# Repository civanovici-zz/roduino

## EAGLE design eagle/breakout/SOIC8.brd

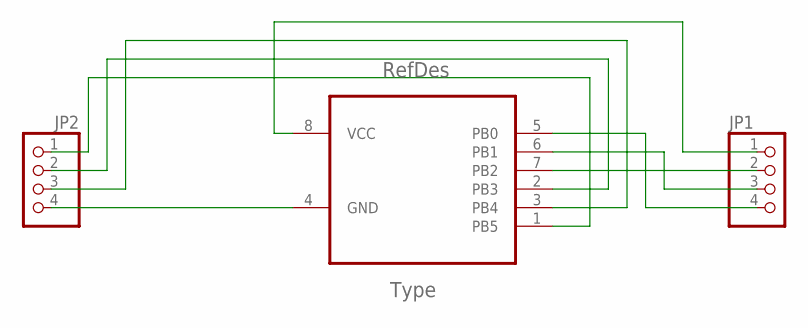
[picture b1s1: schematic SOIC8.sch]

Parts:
JP1, JP2: PINHD-1X4; 1X04
U1: ATTINY13-20SU; SOIC127P798X216-8N

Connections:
unnamed: JP2.1, U1.1 (PB5)
unnamed: JP2.2, U1.2 (PB3)
unnamed: JP2.3, U1.3 (PB4)
unnamed: JP2.4, U1.4 (GND)
unnamed: JP1.4, U1.5 (PB0)
unnamed: JP1.3, U1.6 (PB1)
unnamed: JP1.2, U1.7 (PB2)
unnamed: JP1.1, U1.8 (VCC)

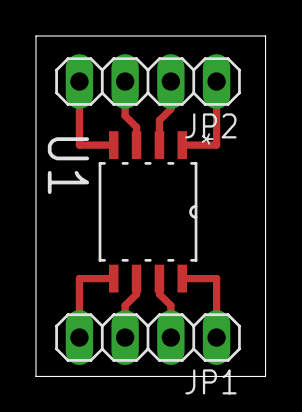
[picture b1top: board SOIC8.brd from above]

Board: 2 copper layers, 12.8 x 18.9 mm, 3 parts (0 on the bottom side), 8 nets.

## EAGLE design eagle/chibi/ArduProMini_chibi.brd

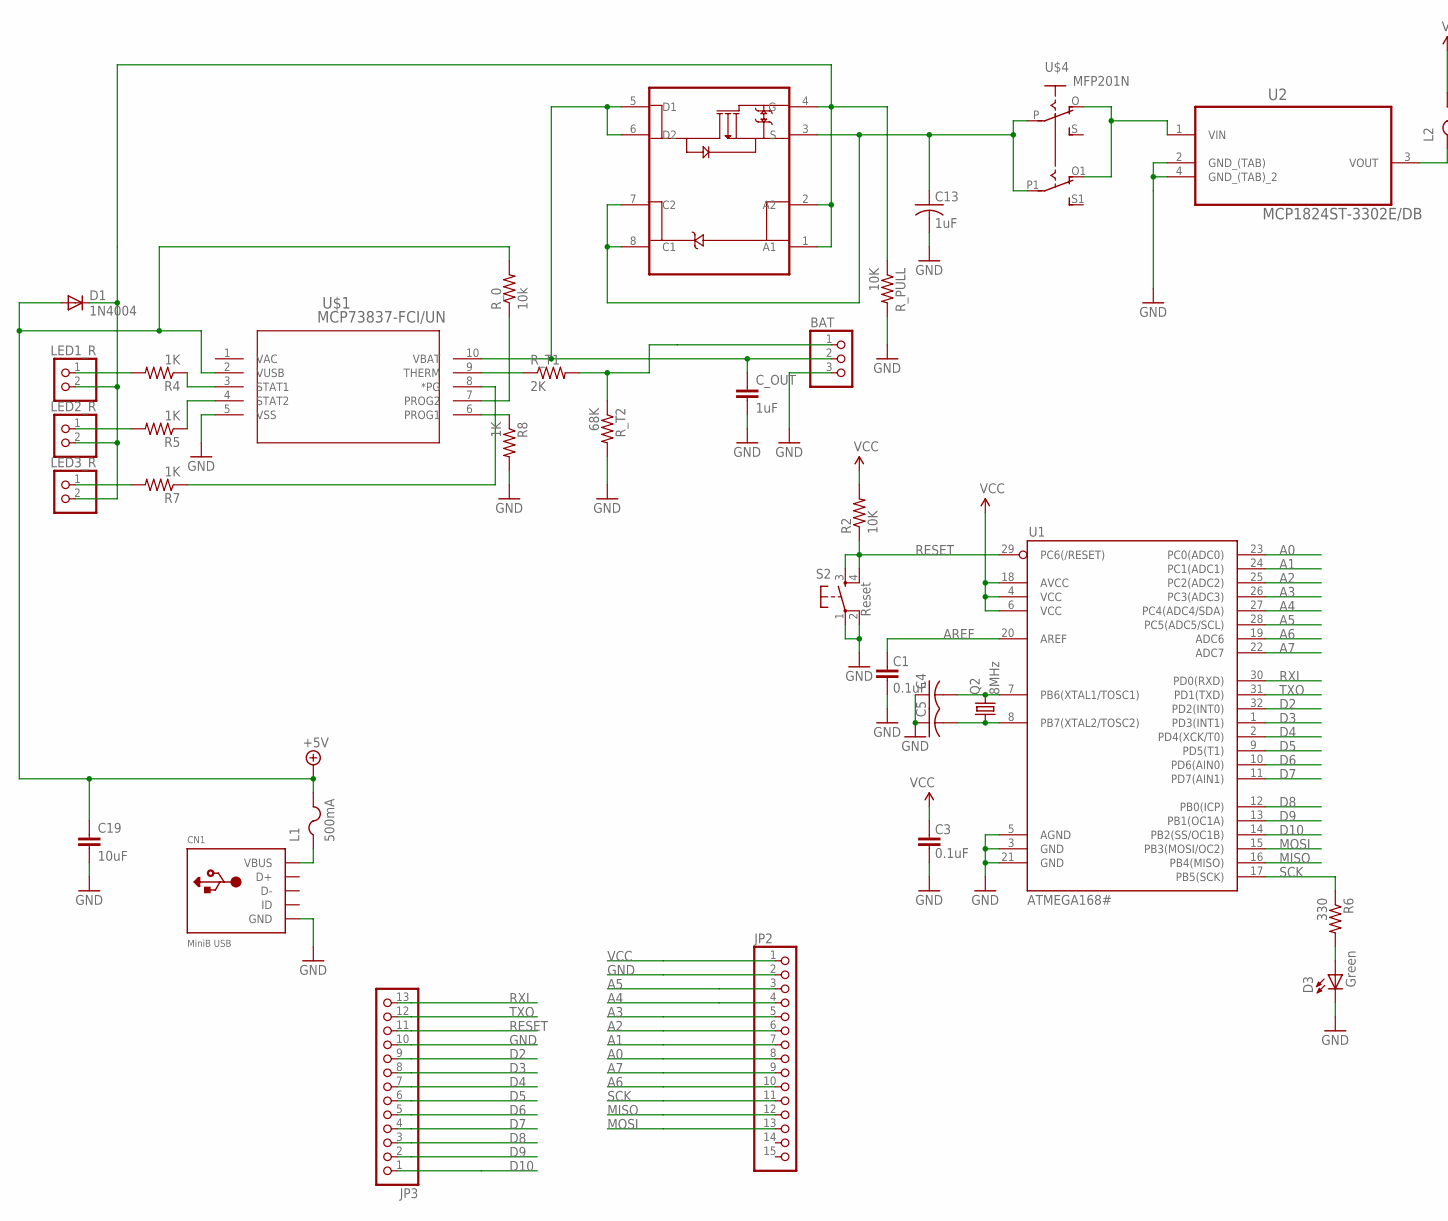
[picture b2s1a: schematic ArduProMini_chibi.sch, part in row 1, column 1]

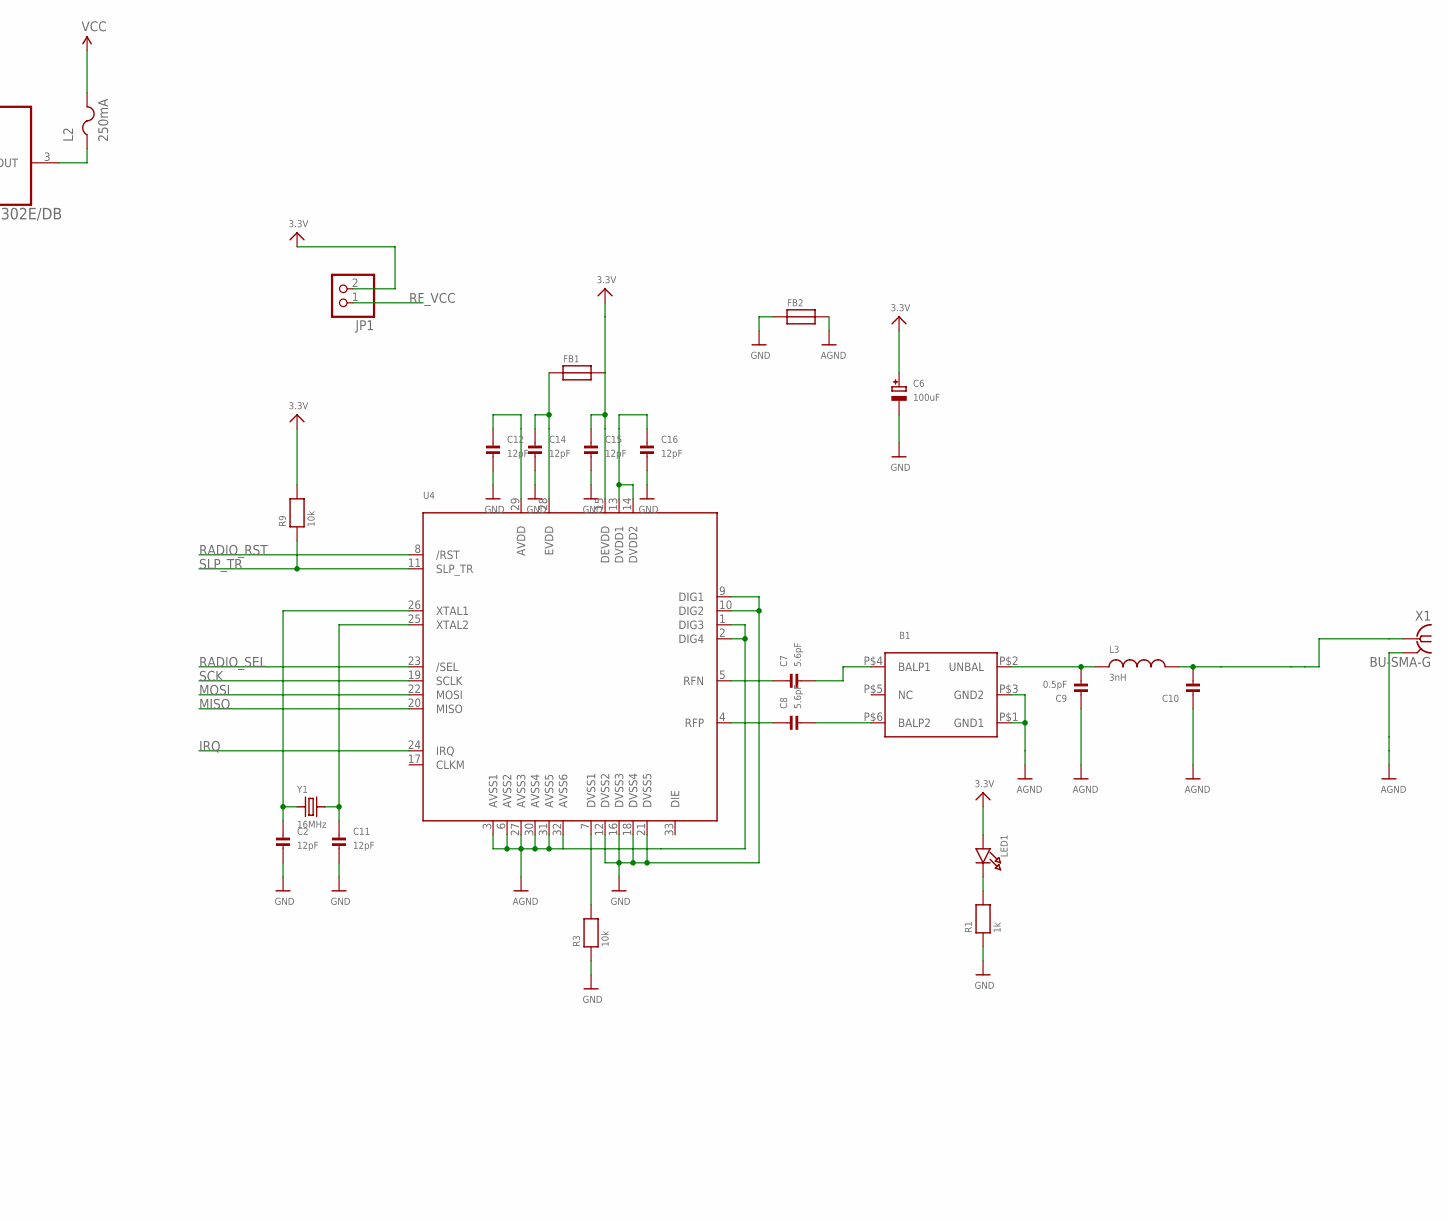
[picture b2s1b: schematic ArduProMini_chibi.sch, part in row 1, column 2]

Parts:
B1: BALUN; BALUN1206
BAT: PINHD-1X3; 1X03
C1, C3: 0.1uF; 0805
C2, C11, C12, C14, C15, C16: 12pF; 0805
C4, C5: C-USC0805; C0805
C6: 100uF; PANASONIC_C
C7, C8: 5.6pF; 0805
C9: 0.5pF; 0805
C10: CAP_CERAMIC0805; 0805
C13: 1uF; C0805
C19: 10uF; C1206
CN1: MiniB USB; USB-MINIB
C_OUT: 1uF; 0805
D1: 1N4004; DO41-10
D3: Green; LED-0603
FB1, FB2: FERRITE; 0603
JP1: PINHD-1X2; 1X02
JP2: PINHD-1X15; 1X15
JP3: PINHD-1X13; 1X13
L1: 500mA; R1206
L2: 250mA; R1206
L3: 3nH; 0805
LED1: LED0805; CHIPLED_0805
LED1_R, LED2_R, LED3_R: PINHD-1X2; 1X02
Q2: 8MHz; CTS406
R1: 1k; 0805
R2: 10K; 0805
R3, R9: 10k; 0805
R4, R5, R7, R8: 1K; 0805
R6: 330; 0805
R_0: 10k; 0805
R_PULL: 10K; 0805
R_T1: 2K; 0805
R_T2: 68K; 0805
S2: Reset; TACTILE_SWITCH_SMD
U1: ATMEGA168#; TQFP32-08
U2: MCP1824ST-3302E/DB; SOT230P700X180-4N
U4: AT86RF212; 32QN2
U$1: MCP73837-FCI/UN; SOP50P490X110-8N
U$3: FDFS2P753Z; SOIC127P600X175-8N
U$4: MFP201N
X1: BU-SMA-G
Y1: 16MHz; HC49UP

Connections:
+5V: C19.1, D1.A, L1.2, R_0.2, U$1.2 (VUSB)
A0: JP2.8, U1.23 (PC0(ADC0))
A1: JP2.7, U1.24 (PC1(ADC1))
A2: JP2.6, U1.25 (PC2(ADC2))
A3: JP2.5, U1.26 (PC3(ADC3))
A4: JP2.4, U1.27 (PC4(ADC4/SDA))
A5: JP2.3, U1.28 (PC5(ADC5/SCL))
A6: JP2.10, U1.19 (ADC6)
A7: JP2.9, U1.22 (ADC7)
AGND: B1.P$1 (GND1), B1.P$3 (GND2), C9.1, C10.1, FB2.2, U4.1 (DIG3), U4.2 (DIG4), U4.3 (AVSS1), U4.6 (AVSS2), U4.27 (AVSS3), U4.30 (AVSS4), U4.31 (AVSS5), U4.32 (AVSS6), X1.2 (GND)
AREF: C1.2, U1.20 (AREF)
D2: JP3.9, U1.32 (PD2(INT0))
D3: JP3.8, U1.1 (PD3(INT1))
D4: JP3.7, U1.2 (PD4(XCK/T0))
D5: JP3.6, U1.9 (PD5(T1))
D6: JP3.5, U1.10 (PD6(AIN0))
D7: JP3.4, U1.11 (PD7(AIN1))
D8: JP3.3, U1.12 (PB0(ICP))
D9: JP3.2, U1.13 (PB1(OC1A))
D10: JP3.1, U1.14 (PB2(SS/OC1B))
GND: BAT.3, C1.1, C2.2, C3.1, C4.1, C5.1, C6.-, C11.2, C12.2, C13.2, C14.2, C15.2, C16.2, C19.2, CN1.GND, C_OUT.2, D3.C, FB2.1, JP2.2, JP3.10, R1.1, R3.1, R8.2, R_PULL.2, R_T2.2, S2.1, S2.2, U1.3 (GND), U1.5 (AGND), U1.21 (GND), U2.2 (GND_(TAB)), U2.4 (GND_(TAB)_2), U4.9 (DIG1), U4.10 (DIG2), U4.12 (DVSS2), U4.16 (DVSS3), U4.18 (DVSS4), U4.21 (DVSS5), U$1.5 (VSS), X1.3 (GND), X1.4 (GND), X1.5 (GND)
IRQ: U4.24 (IRQ)
MISO: JP2.12, U1.16 (PB4(MISO)), U4.20 (MISO)
MOSI: JP2.13, U1.15 (PB3(MOSI/OC2)), U4.22 (MOSI)
unnamed: C5.2, Q2.1, U1.8 (PB7(XTAL2/TOSC2))
unnamed: U2.1 (VIN), U$4.O, U$4.O1
unnamed: C4.2, Q2.3 (2), U1.7 (PB6(XTAL1/TOSC1))
unnamed: R_T1.1, U$1.9 (THERM)
unnamed: R7.1, U$1.8 (*PG)
unnamed: C13.1, U$3.3 (S), U$3.7 (C2), U$3.8 (C1), U$4.P, U$4.P1
unnamed: D3.A, R6.2
unnamed: LED3_R.1, R7.2
unnamed: BAT.2, C_OUT.1, U$1.10 (VBAT), U$3.5 (D1), U$3.6 (D2)
unnamed: L2.1, U2.3 (VOUT)
unnamed: D1.C, LED1_R.2, LED2_R.2, LED3_R.2, R_PULL.1, U$3.1 (A1), U$3.2 (A2), U$3.4 (G)
unnamed: LED2_R.1, R5.2
unnamed: LED1_R.1, R4.2
unnamed: R5.1, U$1.4 (STAT2)
unnamed: R4.1, U$1.3 (STAT1)
unnamed: BAT.1, R_T1.2, R_T2.1
unnamed: C7.1, U4.5 (RFN)
unnamed: R8.1, U$1.6 (PROG1)
unnamed: R_0.1, U$1.7 (PROG2)
unnamed: C8.1, U4.4 (RFP)
unnamed: B1.P$4 (BALP1), C7.2
unnamed: B1.P$6 (BALP2), C8.2
unnamed: B1.P$2 (UNBAL), C9.2, L3.1
unnamed: C10.2, L3.2, X1.1
unnamed: LED1.C, R1.2
unnamed: C2.1, U4.26 (XTAL1), Y1.1
unnamed: C11.1, U4.25 (XTAL2), Y1.2
unnamed: R3.2, U4.7 (DVSS1)
unnamed: C16.1, U4.13 (DVDD1), U4.14 (DVDD2)
unnamed: C14.1, FB1.1, U4.28 (EVDD)
unnamed: C12.1, U4.29 (AVDD)
RADIO_RST: U4.8 (/RST)
RADIO_SEL: U4.23 (/SEL)
RESET: JP3.11, R2.1, S2.3, S2.4, U1.29 (PC6(/RESET))
RF_VCC: C6.+, C15.1, FB1.2, JP1.1, LED1.A, R9.2, U4.15 (DEVDD)
RXI: JP3.13, U1.30 (PD0(RXD))
SCK: JP2.11, R6.1, U1.17 (PB5(SCK)), U4.19 (SCLK)
SLP_TR: R9.1, U4.11 (SLP_TR)
TXO: JP3.12, U1.31 (PD1(TXD))
VBUS: CN1.VBUS, L1.1
VCC: C3.2, JP1.2, JP2.1, L2.2, R2.2, U1.4 (VCC), U1.6 (VCC), U1.18 (AVCC)

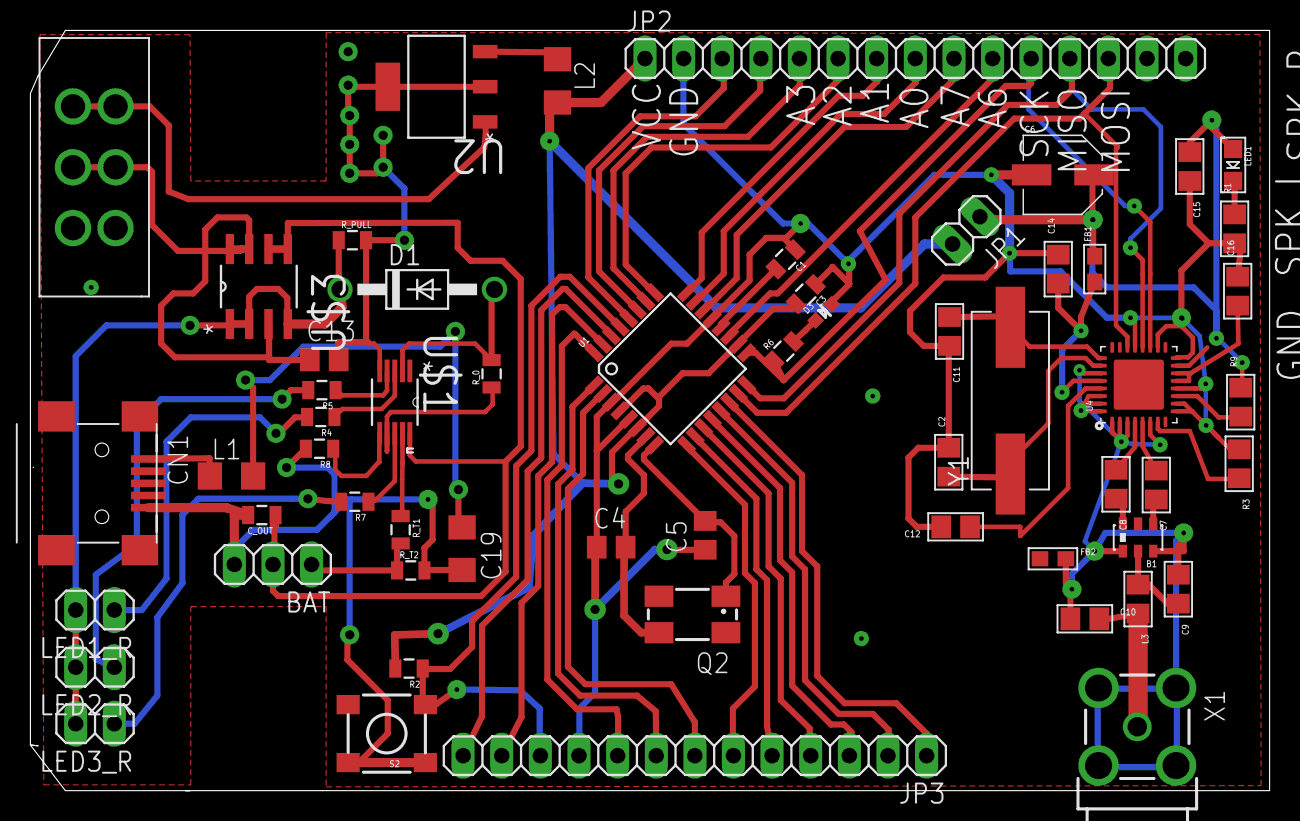
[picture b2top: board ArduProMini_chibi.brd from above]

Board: 2 copper layers, 81.5 x 50.0 mm, 58 parts (0 on the bottom side), 62 nets.

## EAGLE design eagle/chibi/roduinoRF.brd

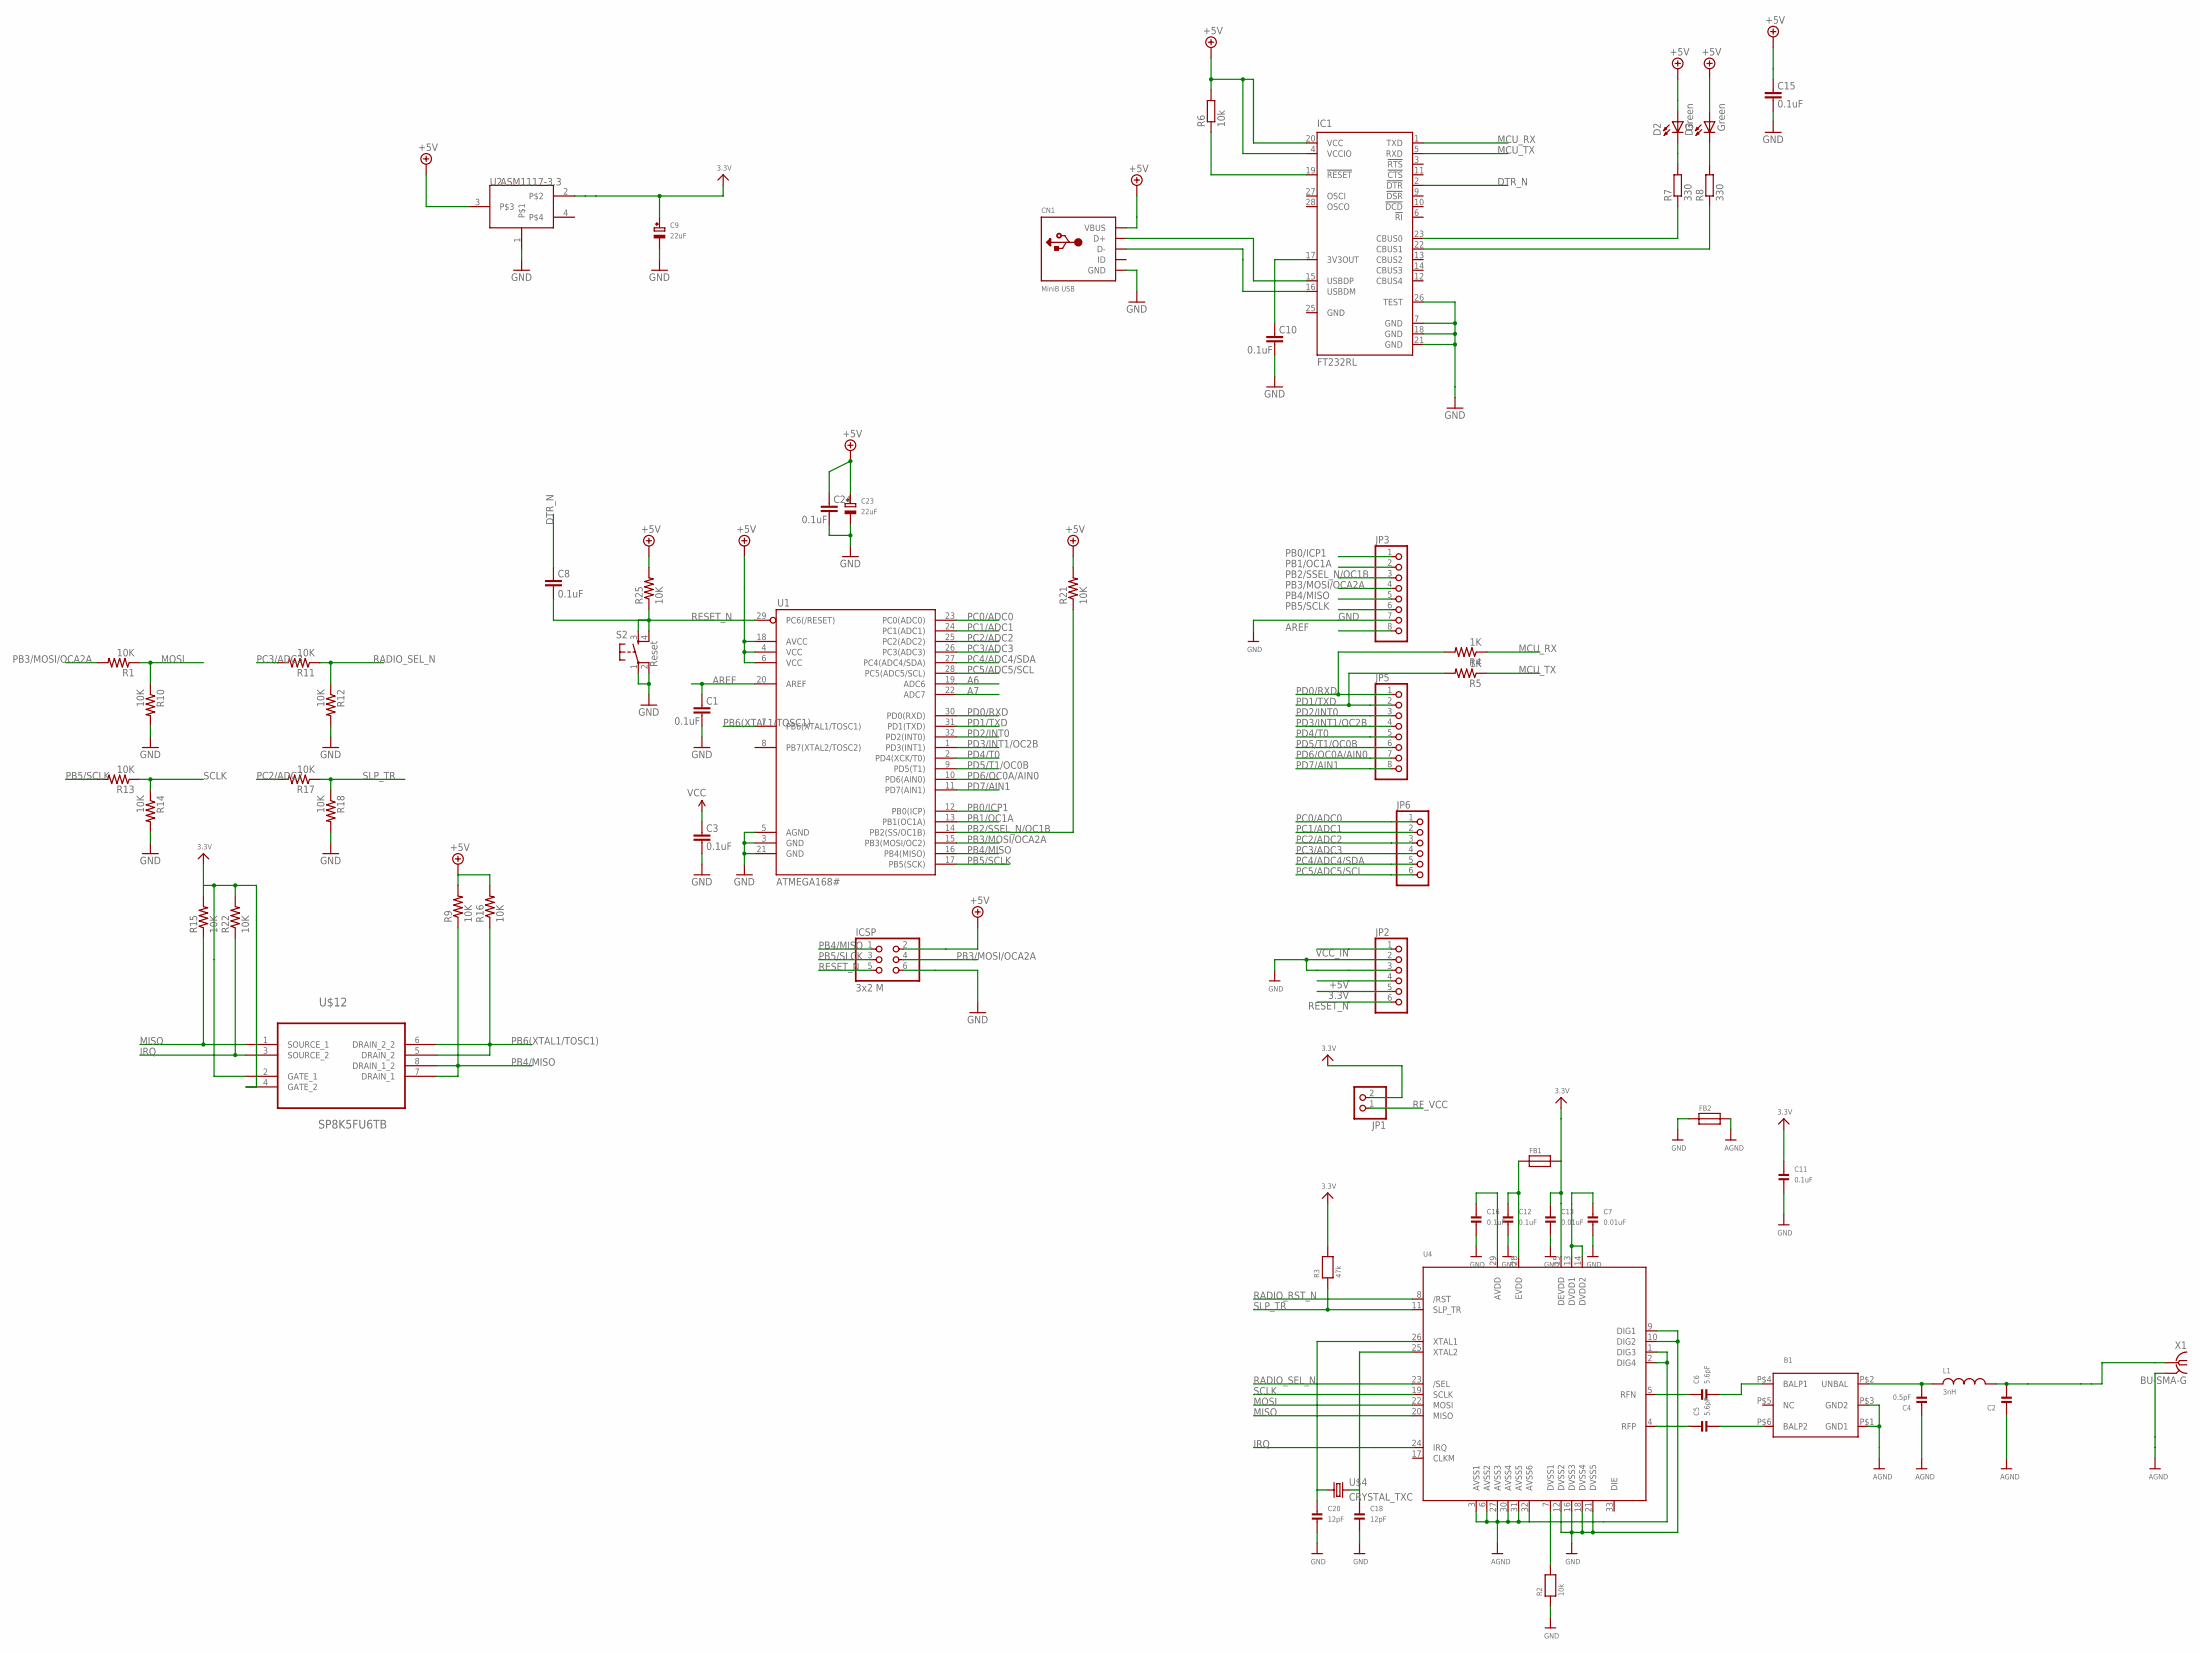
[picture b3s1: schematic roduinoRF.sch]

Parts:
B1: BALUN; BALUN1206
C1, C3, C8, C10, C11, C12, C15, C16, C24: 0.1uF; 0805
C2: CAP_CERAMIC0805; 0805
C4: 0.5pF; 0805
C5, C6: 5.6pF; 0805
C7, C13: 0.01uF; 0805
C9, C23: 22uF; PANASONIC_C
C18, C20: 12pF; 0805
CN1: MiniB USB; USB-MINIB
D2, D3: Green; LED-0603
FB1, FB2: FERRITE; 0603
IC1: FT232RL; SSOP28
ICSP: 3x2 M; 2X03
JP1: PINHD-1X2; 1X02
JP2, JP6: PINHD-1X6; 1X06
JP3, JP5: PINHD-1X8; 1X08
L1: 3nH; 0805
R1, R9, R10, R11, R12, R13, R14, R15, R16, R17, R18, R21, R22, R25: 10K; 0805
R2: 10k; 0805
R3: 47k; 0805
R4, R5: 1K; 0805
R6: 10k; R0603
R7, R8: 330; R0805
S2: Reset; TACTILE_SWITCH_SMD
U1: ATMEGA168#; TQFP32-08
U2: ASM1117-3.3; SOT223
U4: AT86RF212; 32QN2
U$4: CRYSTAL_TXC; CRYSTAL_TCX
U$12: SP8K5FU6TB; SOP127P600X175-8N
X1: BU-SMA-G

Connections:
3.3V: C9.+, JP1.2, JP2.5, R15.2, R22.2, U2.2, U$12.2 (GATE_1), U$12.4 (GATE_2)
+5V: C3.2, C15.2, C23.+, C24.2, CN1.VBUS, D2.A, D3.A, IC1.4 (VCCIO), IC1.20 (VCC), ICSP.2, JP2.4, R6.2, R9.2, R16.2, R21.2, R25.2, U1.4 (VCC), U1.6 (VCC), U1.18 (AVCC), U2.3
A6: U1.19 (ADC6)
A7: U1.22 (ADC7)
AGND: B1.P$1 (GND1), B1.P$3 (GND2), C2.1, C4.1, FB2.2, U4.1 (DIG3), U4.2 (DIG4), U4.3 (AVSS1), U4.6 (AVSS2), U4.27 (AVSS3), U4.30 (AVSS4), U4.31 (AVSS5), U4.32 (AVSS6), X1.2 (GND)
AREF: C1.2, JP3.8, U1.20 (AREF)
DTR_N: C8.2, IC1.2 (!DTR)
GND: C1.1, C3.1, C7.2, C9.-, C10.1, C11.2, C12.2, C13.2, C15.1, C16.2, C18.2, C20.2, C23.-, C24.1, CN1.GND, FB2.1, IC1.7 (GND), IC1.18 (GND), IC1.21 (GND), IC1.25 (GND), IC1.26 (TEST), ICSP.6, JP2.2, JP2.3, JP3.7, R2.1, R10.2, R12.2, R14.2, R18.2, S2.1, S2.2, U1.3 (GND), U1.5 (AGND), U1.21 (GND), U2.1, U4.9 (DIG1), U4.10 (DIG2), U4.12 (DVSS2), U4.16 (DVSS3), U4.18 (DVSS4), U4.21 (DVSS5), X1.3 (GND), X1.4 (GND), X1.5 (GND)
GND1: D2.C, R7.2
IRQ: R22.1, U4.24 (IRQ), U$12.3 (SOURCE_2)
MCU_RX: IC1.1 (TXD), R4.1
MCU_TX: IC1.5 (RXD), R5.1
MISO: R15.1, U4.20 (MISO), U$12.1 (SOURCE_1)
MOSI: R1.1, R10.1, U4.22 (MOSI)
unnamed: CN1.D+, IC1.15 (USBDP)
unnamed: CN1.D-, IC1.16 (USBDM)
unnamed: IC1.23 (CBUS0), R7.1
unnamed: IC1.19 (!RESET), R6.1
unnamed: IC1.22 (CBUS1), R8.1
unnamed: D3.C, R8.2
unnamed: C10.2, IC1.17 (3V3OUT)
unnamed: C6.1, U4.5 (RFN)
unnamed: C5.1, U4.4 (RFP)
unnamed: B1.P$4 (BALP1), C6.2
unnamed: B1.P$6 (BALP2), C5.2
unnamed: B1.P$2 (UNBAL), C4.2, L1.1
unnamed: C2.2, L1.2, X1.1
unnamed: C20.1, U4.26 (XTAL1), U$4.1
unnamed: C18.1, U4.25 (XTAL2), U$4.2
unnamed: R2.2, U4.7 (DVSS1)
unnamed: C7.1, U4.13 (DVDD1), U4.14 (DVDD2)
unnamed: C12.1, FB1.1, U4.28 (EVDD)
unnamed: C16.1, U4.29 (AVDD)
PB0/ICP1: JP3.1, U1.12 (PB0(ICP))
PB1/OC1A: JP3.2, U1.13 (PB1(OC1A))
PB2/SSEL_N/OC1B: JP3.3, R21.1, U1.14 (PB2(SS/OC1B))
PB3/MOSI/OCA2A: ICSP.4, JP3.4, R1.2, U1.15 (PB3(MOSI/OC2))
PB4/MISO: ICSP.1, JP3.5, R9.1, U1.16 (PB4(MISO)), U$12.7 (DRAIN_1), U$12.8 (DRAIN_1_2)
PB5/SCLK: JP3.6, R13.2, U1.17 (PB5(SCK))
PB5/SLCK: ICSP.3
PB6(XTAL1/TOSC1): R16.1, U1.7 (PB6(XTAL1/TOSC1)), U$12.5 (DRAIN_2), U$12.6 (DRAIN_2_2)
PC0/ADC0: JP6.1, U1.23 (PC0(ADC0))
PC1/ADC1: JP6.2, U1.24 (PC1(ADC1))
PC2/ADC2: JP6.3, R17.2, U1.25 (PC2(ADC2))
PC3/ADC3: JP6.4, R11.2, U1.26 (PC3(ADC3))
PC4/ADC4/SDA: JP6.5, U1.27 (PC4(ADC4/SDA))
PC5/ADC5/SCL: JP6.6, U1.28 (PC5(ADC5/SCL))
PD0/RXD: JP5.1, R4.2, U1.30 (PD0(RXD))
PD1/TXD: JP5.2, R5.2, U1.31 (PD1(TXD))
PD2/INT0: JP5.3, U1.32 (PD2(INT0))
PD3/INT1/OC2B: JP5.4, U1.1 (PD3(INT1))
PD4/T0: JP5.5, U1.2 (PD4(XCK/T0))
PD5/T1/OC0B: JP5.6, U1.9 (PD5(T1))
PD6/OC0A/AIN0: JP5.7, U1.10 (PD6(AIN0))
PD7/AIN1: JP5.8, U1.11 (PD7(AIN1))
RADIO_RST_N: U4.8 (/RST)
RADIO_SEL_N: R11.1, R12.1, U4.23 (/SEL)
RESET_N: C8.1, ICSP.5, JP2.6, R25.1, S2.3, S2.4, U1.29 (PC6(/RESET))
RF_VCC: C11.1, C13.1, FB1.2, JP1.1, R3.2, U4.15 (DEVDD)
SCLK: R13.1, R14.1, U4.19 (SCLK)
SLP_TR: R3.1, R17.1, R18.1, U4.11 (SLP_TR)
VCC_IN: JP2.1

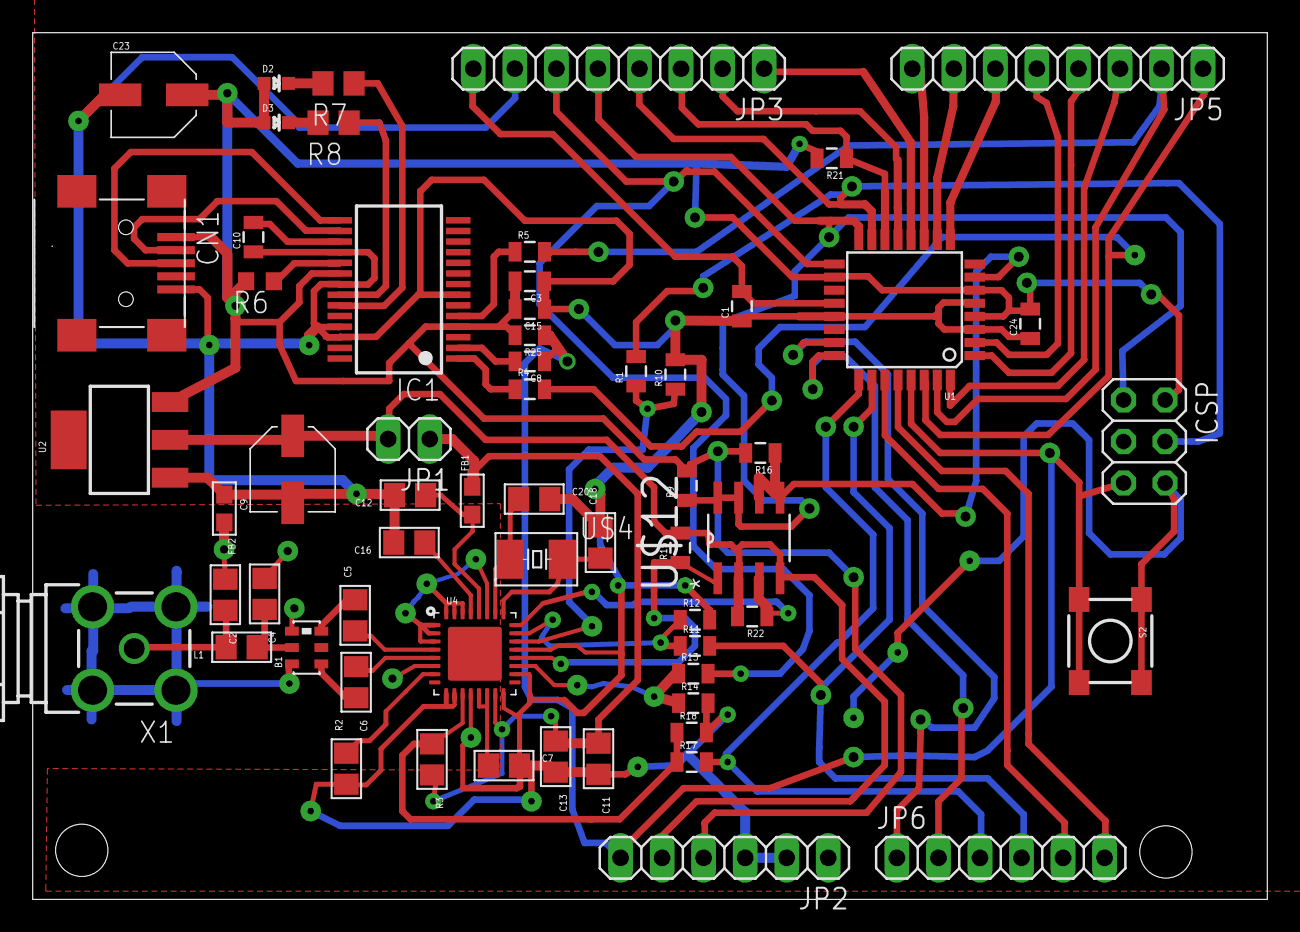
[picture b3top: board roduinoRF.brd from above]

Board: 2 copper layers, 75.5 x 53.0 mm, 61 parts (0 on the bottom side), 57 nets.

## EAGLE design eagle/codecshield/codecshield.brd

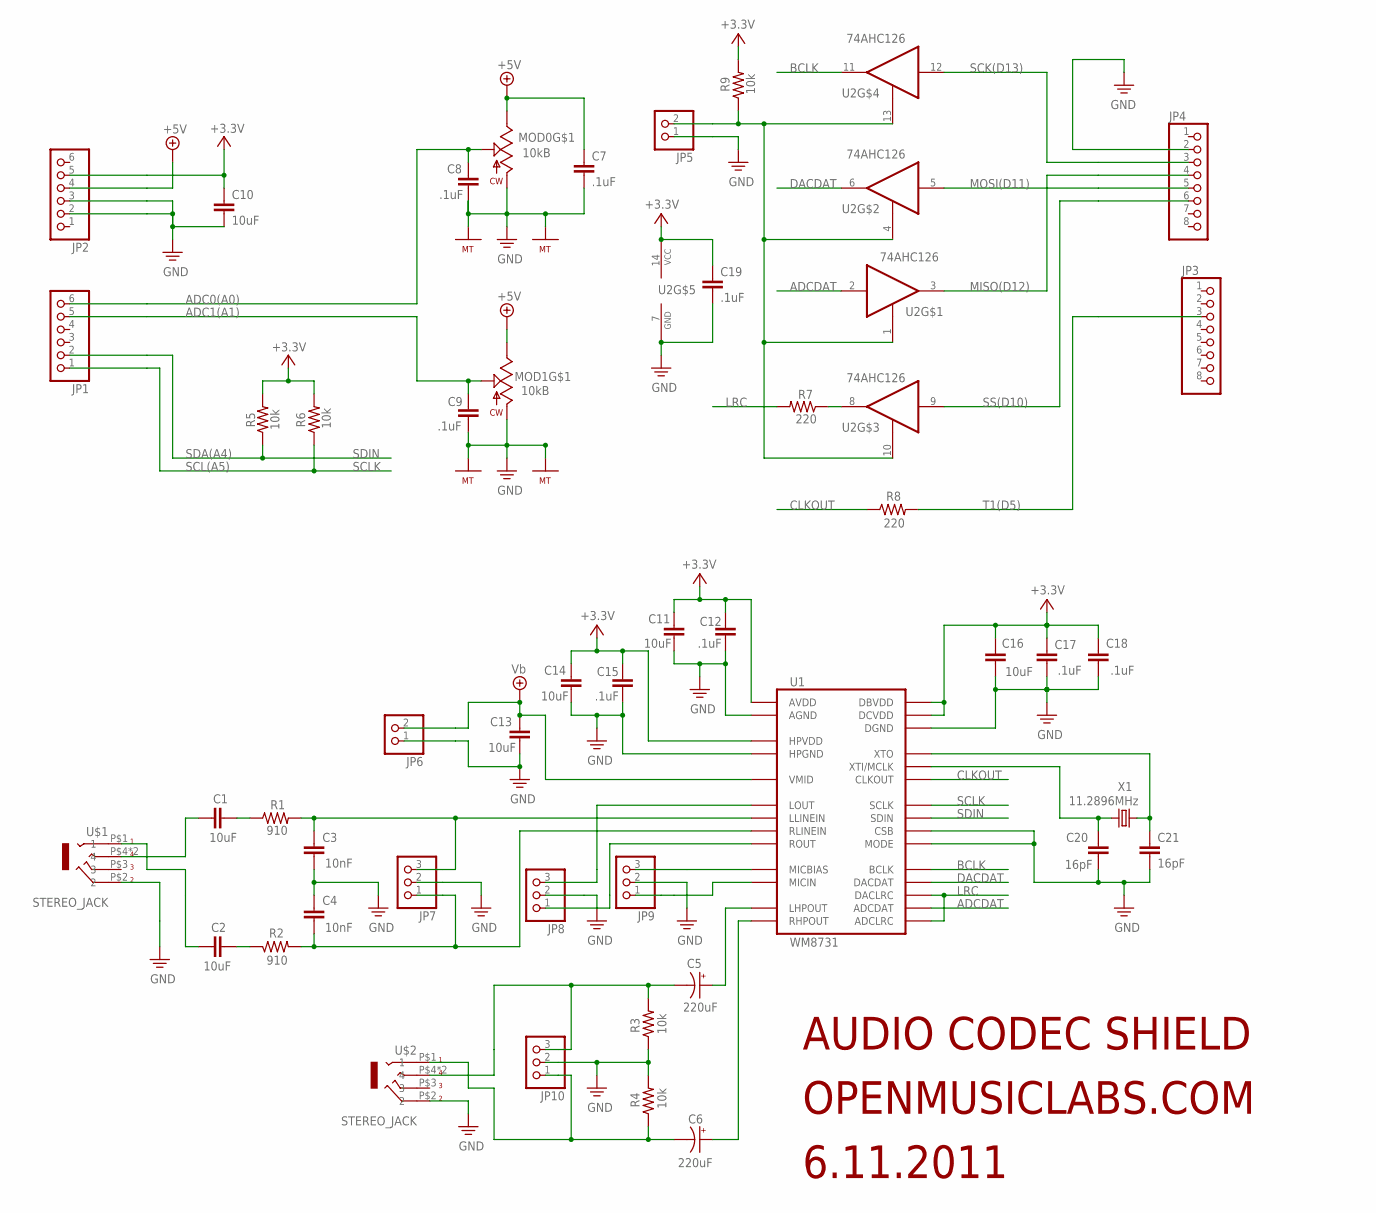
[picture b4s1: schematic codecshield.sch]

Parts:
C1, C2, C10, C11, C13, C14, C16: 10uF; 0805A
C3, C4: 10nF; 0805A
C5, C6: 220uF; CAP/6.3MMX2.5MM
C7, C8, C9, C12, C15, C17, C18, C19: .1uF; 0805A
C20, C21: 16pF; 0805A
JP1, JP2: PINHD-1X6; 1X06
JP3, JP4: PINHD-1X8; 1X08
JP5, JP6: PINHD-1X2; 1X02
JP7, JP8, JP9, JP10: PINHD-1X3; 1X03
MOD0, MOD1: 10kB; POT/SINGLE/ALPHA/VERT
R1, R2: 910; 0805A
R3, R4, R5, R6, R9: 10k; 0805A
R7, R8: 220; 0805A
U1: WM8731; 28-SSOP
U2: 74AHC126; 14-SOIC
U$1, U$2: STEREO_JACK; JACK_STEREO
X1: 11.2896MHz; HC49U/SMT

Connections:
+5V: C7.+ (1), JP2.4, MOD0.P$3 (3), MOD1.P$3 (3)
+5V/1: C13.- (2), JP6.2, U1.P$16 (VMID)
ADCDAT: U1.P$6 (ADCDAT), U2.2 (I)
BCLK: U1.P$3 (BCLK), U2.11 (O)
CLKOUT: R8.+ (1), U1.P$2 (CLKOUT)
DACDAT: U1.P$4 (DACDAT), U2.6 (O)
LINE_IN: C1.+ (1), U$1.P$4 (4), U$1.P$5 (4)
LRC: R7.- (2), U1.P$5 (DACLRC), U1.P$7 (ADCLRC)
unnamed: C5.P$1 (+), U1.P$9 (LHPOUT)
unnamed: C6.P$1 (+), U1.P$10 (RHPOUT)
unnamed: JP9.1, U1.P$18 (MICIN)
unnamed: C1.- (2), R1.+ (1)
unnamed: C5.P$2 (-), JP10.3, R3.- (2), U$2.P$4 (4), U$2.P$5 (4)
unnamed: C6.P$2 (-), JP10.1, R4.+ (1), U$2.P$1 (1)
unnamed: JP8.3, U1.P$12 (LOUT)
unnamed: JP3.3, R8.- (2)
unnamed: JP8.1, U1.P$13 (ROUT)
unnamed: C3.- (2), JP7.3, R1.- (2), U1.P$20 (LLINEIN)
unnamed: JP4.6, U2.9 (I)
unnamed: JP4.3, U2.12 (I)
unnamed: JP5.2, R9.+ (1), U2.1 (OE), U2.4 (OE), U2.10 (OE), U2.13 (OE)
unnamed: C2.- (2), U$1.P$1 (1)
unnamed: C2.+ (1), R2.+ (1)
unnamed: C8.- (2), JP1.6, MOD0.P$2 (2)
unnamed: C9.+ (1), JP1.5, MOD1.P$2 (2)
unnamed: C4.- (2), JP7.1, R2.- (2), U1.P$19 (RLINEIN)
unnamed: JP9.3, U1.P$17 (MICBIAS)
unnamed: JP4.5, U2.5 (I)
unnamed: C20.+ (1), U1.P$25 (XTI/MCLK), X1.1
unnamed: C21.+ (1), U1.P$26 (XTO), X1.2
unnamed: JP4.4, U2.3 (O)
unnamed: R7.+ (1), U2.8 (O)
PE: C3.+ (1), C4.+ (1), C7.- (2), C8.+ (1), C9.- (2), C10.- (2), C11.+ (1), C12.+ (1), C13.+ (1), C14.+ (1), C15.+ (1), C16.+ (1), C17.+ (1), C18.+ (1), C19.- (2), C20.- (2), C21.- (2), JP2.2, JP2.3, JP4.2, JP5.1, JP6.1, JP7.2, JP8.2, JP9.2, JP10.2, MOD0.P$1 (1), MOD0.P$4 (MT), MOD0.P$5 (MT), MOD1.P$1 (1), MOD1.P$4 (MT), MOD1.P$5 (MT), R3.+ (1), R4.- (2), U1.P$11 (HPGND), U1.P$15 (AGND), U1.P$21 (MODE), U1.P$22 (CSB), U1.P$28 (DGND), U2.7 (GND), U$1.P$2 (2), U$2.P$2 (2)
SCLK: JP1.1, R6.+ (1), U1.P$24 (SCLK)
SDIN: JP1.2, R5.+ (1), U1.P$23 (SDIN)
VCC: C10.+ (1), C11.- (2), C12.- (2), C14.- (2), C15.- (2), C16.- (2), C17.- (2), C18.- (2), C19.+ (1), JP2.5, R5.- (2), R6.- (2), R9.- (2), U1.P$1 (DBVDD), U1.P$8 (HPVDD), U1.P$14 (AVDD), U1.P$27 (DCVDD), U2.14 (VCC)

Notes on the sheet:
AUDIO CODEC SHIELD
OPENMUSICLABS.COM
6.11.2011
ADC0(A0)
ADC1(A1)
T1(D5)
SS(D10)
MOSI(D11)
MISO(D12)
SCK(D13)
SCL(A5)
SDA(A4)

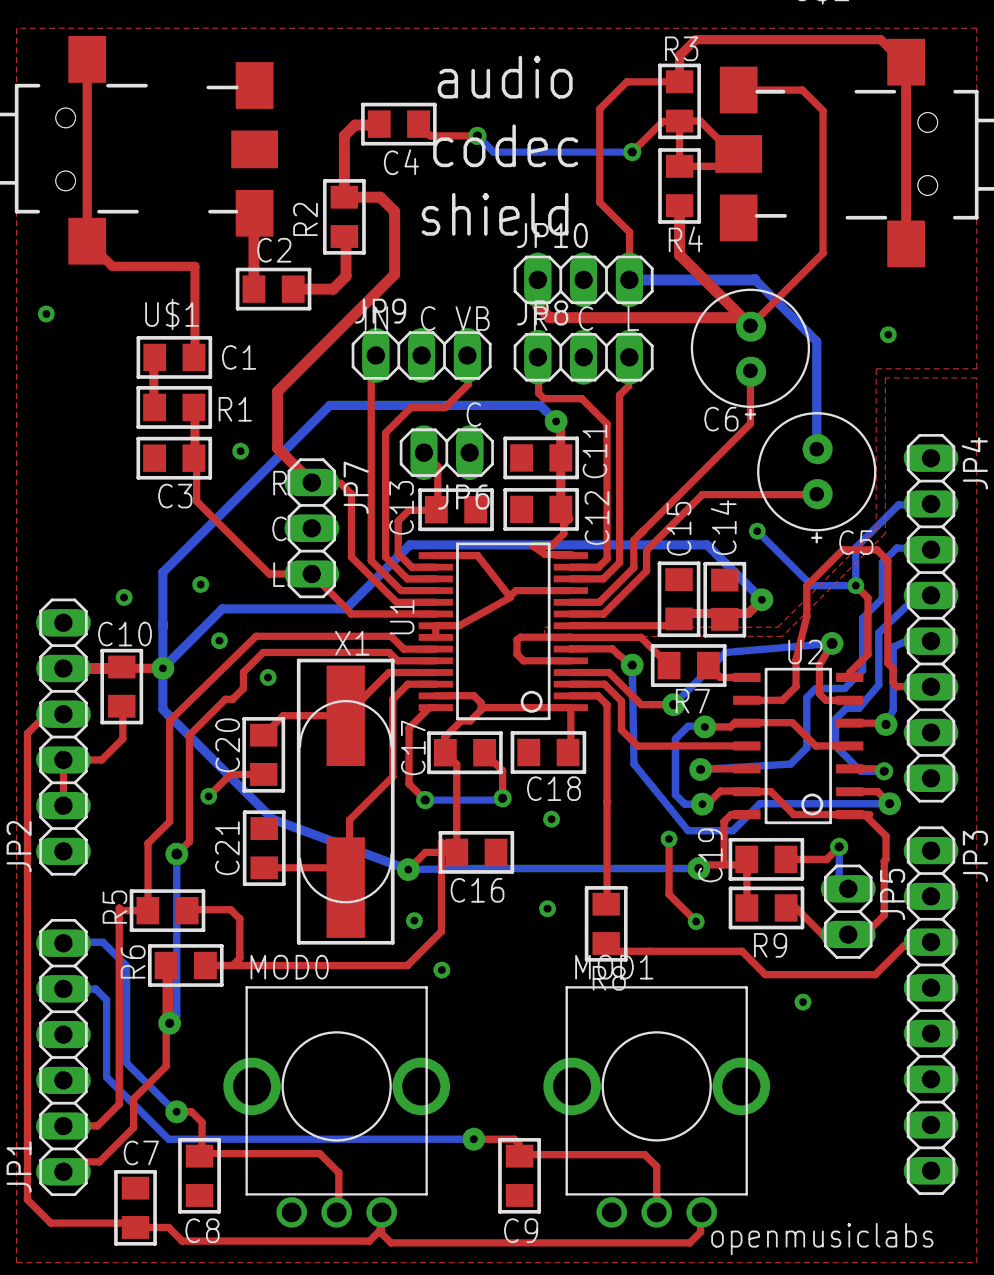
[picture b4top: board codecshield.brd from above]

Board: 2 copper layers, 47 parts (0 on the bottom side), 36 nets.

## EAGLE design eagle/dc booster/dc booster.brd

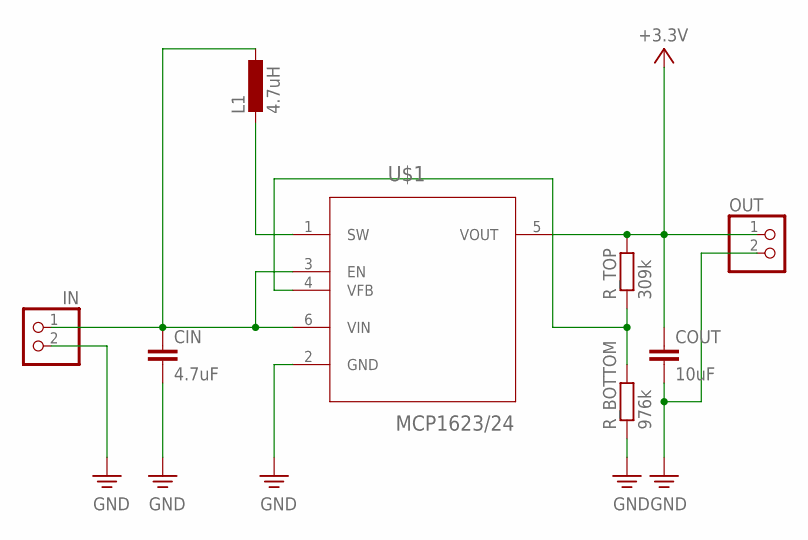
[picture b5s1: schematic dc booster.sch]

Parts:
CIN: 4.7uF; C0805
COUT: 10uF; C0805
IN: PINHD-1X2; 1X02
L1: 4.7uH; POWER-CHOKE_WE-TPC
OUT: PINHD-1X2; 1X02
R_BOTTOM: 976k; R0805
R_TOP: 309k; R0805
U$1: MCP1623/24; SOT95P300X120-6N

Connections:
unnamed: CIN.1, IN.1, L1.1, U$1.3 (EN), U$1.6 (VIN)
unnamed: L1.2, U$1.1 (SW)
unnamed: R_BOTTOM.2, R_TOP.1, U$1.4 (VFB)
PE: CIN.2, COUT.2, IN.2, OUT.2, R_BOTTOM.1, U$1.2 (GND)
VCC: COUT.1, OUT.1, R_TOP.2, U$1.5 (VOUT)

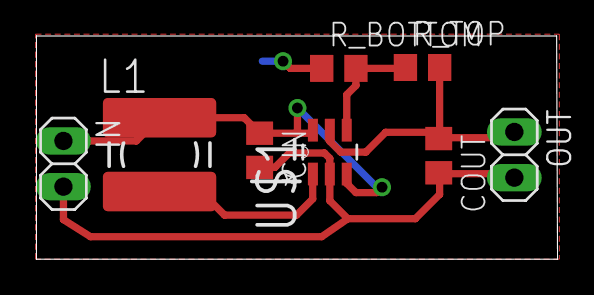
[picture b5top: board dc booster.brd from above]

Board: 2 copper layers, 28.9 x 12.4 mm, 8 parts (0 on the bottom side), 5 nets.

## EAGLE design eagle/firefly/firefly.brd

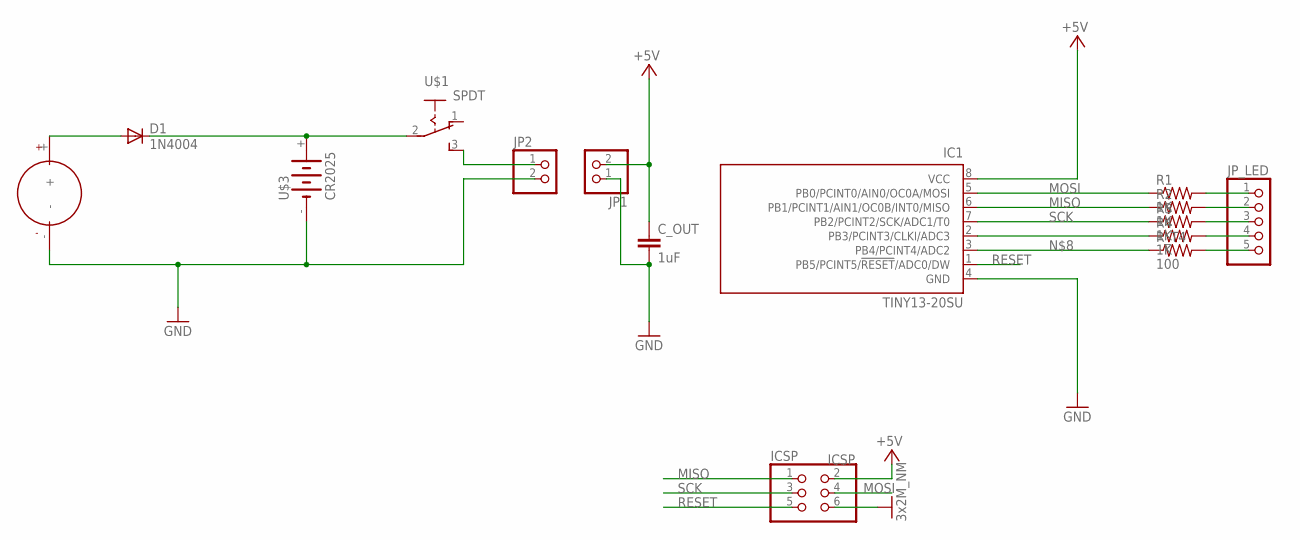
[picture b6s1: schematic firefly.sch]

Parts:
C_OUT: 1uF; 0805
D1: 1N4004; DO41-10
IC1: TINY13-20SU; 8S2
ICSP: ICSP; 2X03
JP1, JP2: PINHD-1X2; 1X02
JP_LED: PINHD-1X5; 1X05
R1, R2, R3, R4: 1K; 0805
R_T4: 100; 0805
U$1: SPDT
U$3: CR2025
U$4: PANEL_60_60

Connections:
+5V: C_OUT.1, IC1.8 (VCC), ICSP.2, JP1.2
GND: C_OUT.2, IC1.4 (GND), ICSP.6, JP1.1, JP2.2, U$3.-, U$4.-
MISO: IC1.6 (PB1/PCINT1/AIN1/OC0B/INT0/MISO), ICSP.1, R2.1
MOSI: IC1.5 (PB0/PCINT0/AIN0/OC0A/MOSI), ICSP.4, R1.1
unnamed: JP_LED.1, R1.2
unnamed: JP_LED.5, R_T4.2
unnamed: D1.A, U$4.+
unnamed: D1.C, U$1.2, U$3.+
unnamed: JP_LED.2, R2.2
unnamed: IC1.2 (PB3/PCINT3/CLKI/ADC3), R4.1
unnamed: JP_LED.3, R3.2
unnamed: IC1.3 (PB4/PCINT4/ADC2), R_T4.1
unnamed: JP2.1, U$1.3 (S)
unnamed: JP_LED.4, R4.2
RESET: IC1.1 (PB5/PCINT5/!RESET!/ADC0/DW), ICSP.5
SCK: IC1.7 (PB2/PCINT2/SCK/ADC1/T0), ICSP.3, R3.1

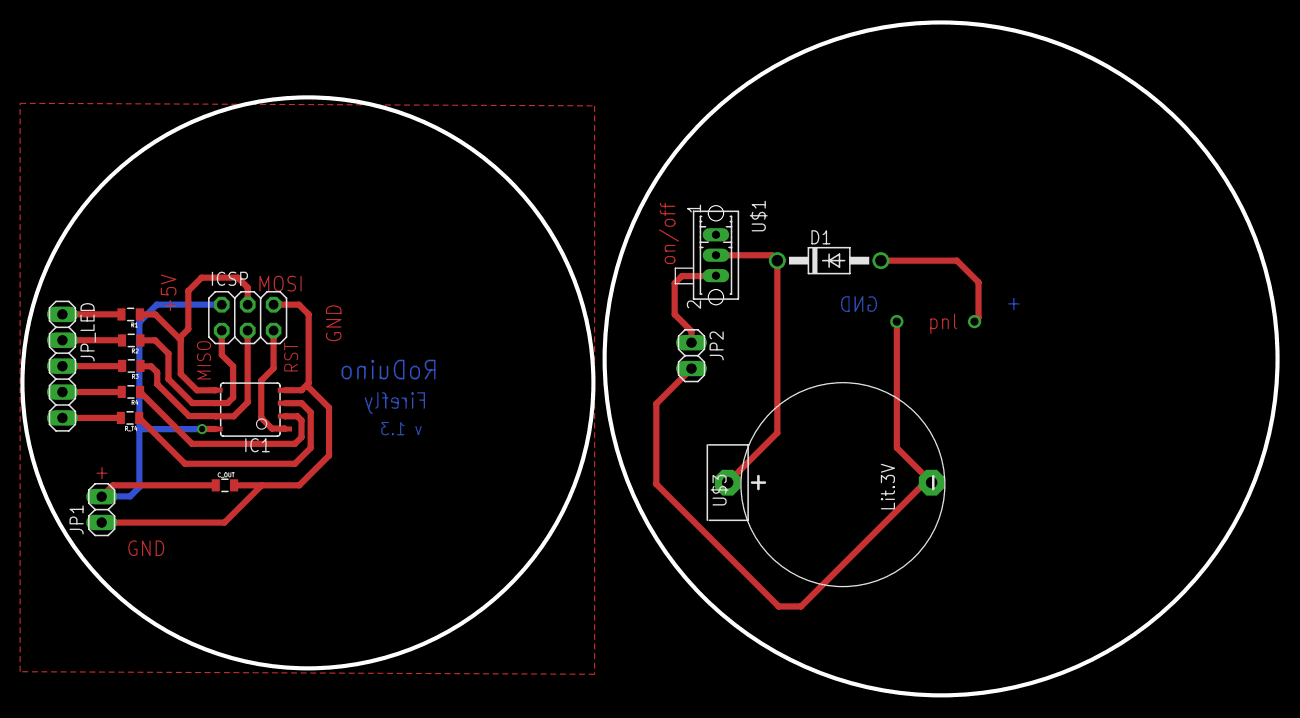
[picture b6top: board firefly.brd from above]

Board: 2 copper layers, 123.1 x 66.0 mm, 15 parts (1 on the bottom side), 16 nets.
